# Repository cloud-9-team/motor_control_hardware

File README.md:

# Control de motores por comunicación Wi-Fi

Este proyecto forma parte de la cátedra de **Taller de Proyecto 1**, perteneciente al segundo semestre de la carrera de Ingeniería en Computación, en la Facultad de Ingeniería de la Universidad de La Plata. 

Nuestra motivación principal es lograr el **control de motores utilizando un tipo de comunicación inalámbrica**. La elección de dicha comunicación debe ser tal que se logre una abstracción del dispositivo desde el cual se envien los comandos de control. 
A partir de estas restricciones elegimos realizar el control de motores de corriente continua mediante el uso del protocolo de comunicación inalámbrica IEEE 802.11, comúnmente conocido cómo Wi-Fi. Al poder abstraernos del dispositivo que envía los comandos, se podrá hacer uso de **smartphones**, **servidores web**, o cualquier otro tipo de dispositivo que cuente con un protocolo de comunicación Wi-Fi integrado.

### Descripción 
En este proyecto se buscará desarrollar específicamente los siguientes puntos:
 - Control de dos motores de corriente continua a través de señales PWM utilizando un H-bridge IC L293D.
 - Comunicación mediante protocolo Wi-Fi con módulo independiente ESP8266.
 - Comunicación serie entre EDU-CIAA y módulo Wi-Fi.
 - Aplicación Android para comunicación con el módulo.

Estos dos últimos ítems se encuentran alojados en el siguiente repositorio https://github.com/cloud-9-team/motor_control_firmware_apps

### Esquema de funcionamiento
El funcionamiento del vehículo será controlado por **instrucciones AT** enviadas inalámbricamente por Wi-Fi desde un smartphone, corriendo un sistema operativo Android, al módulo ESP8266. El módulo ESP8266 enviará las instrucciones por **comunicación serie** a la EDU CIAA-NXP. La EDU CIAA procesará los comandos y, en base a eso, modificará los valores correspondientes de los cuatro outputs de SCT (módulo State Controlled Timer). Las señales serán enviadas a los inputs del H-bridge IC. El H-bridge, en base a la tensión media que reciba por sus entradas, permitirá a los dos motores girar en determinado sentido y con una cierta velocidad. Los sentidos y velocidades de los motores determinarán la dirección de movimiento del vehículo.

### Herramientas de desarrollo
Para el diseño del hardware se utiliza la herramienta de diseño asistido por computadora **Kicad**, y para el desarrollo del software el plugin de la CIAA para el entorno **Eclipse**.

### Integrantes del grupo

 - Julián Ailán
 - Federico Bouche
 - Lucas Hourquebie
 - Emiliano Liotta

### Descarga de los documentos
Debes tener **Git** instalado en tu máquina para poder gestionar las descargas. La instalación de Git depende del sistema operativo que uses
 - Distribuciones de Linux: 
    - En el caso de utilizar Fedora podes utilizar **yum**:
    ```sh
    $ sudo yum install git
    ```
    - En el caso de utilizar distribuciones basadas en Debian tenés que usar **apt-get**:
    ```sh
    $ sudo apt-get install git
    ```
 - Windows: accedé a http://git-scm.com/download/win y la instalación comenzará de forma automática.
 - MacOS: del mismo modo que en Windows, accedé a http://git-scm.com/download/mac y el instalador comenzará a descargarse.

Crear o posicionarse en la carpeta donde se desea descargar el contenido e inicializarla:
```sh
$ mkdir <nombre_de_la_carpeta>
$ cd <nombre_de_la_carpeta>
$ git init
```
Luego se debe relacionar el repositorio con la carpeta donde previamente te situaste:
```sh
$ git remote add origin https://github.com/cloud-9-team/motor_control_hardware.git
```
Por último, los contenidos se descargarán a la carpeta corriendo el siguiente comando:
```sh
$ git pull origin master
```
### Version
1.1

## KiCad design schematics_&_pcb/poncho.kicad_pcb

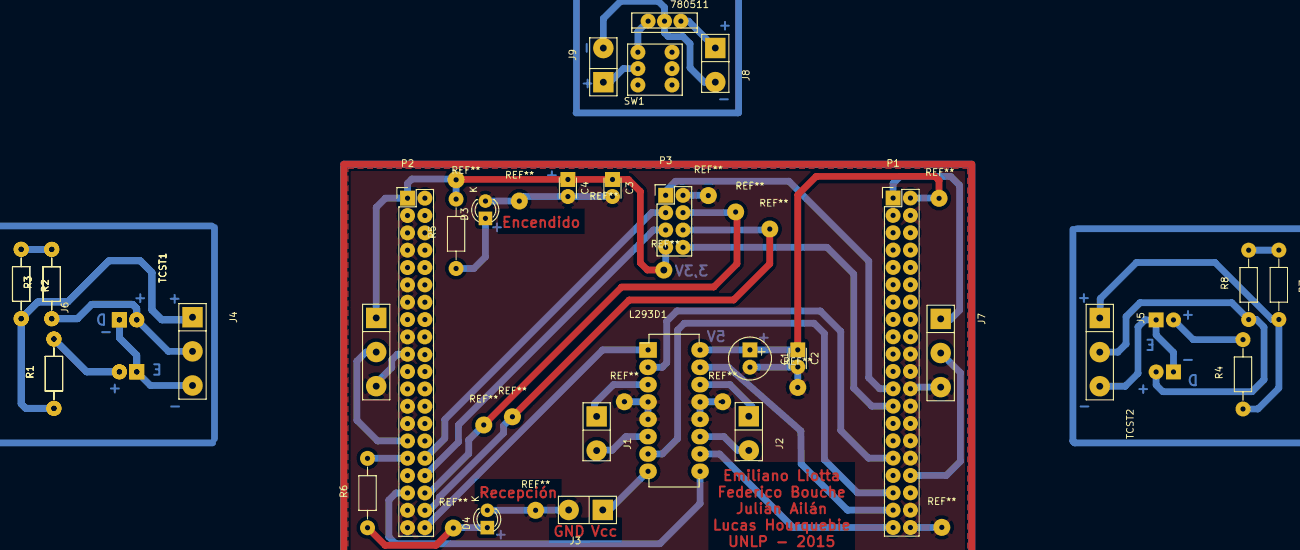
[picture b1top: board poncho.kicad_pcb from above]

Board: 2 copper layers, 35 parts (0 on the bottom side), 32 nets.

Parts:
780511: LM7805reg; LM7805
C1: CP; Elko_vert_11.2x6.3mm_RM2.5
C2, C3, C4: C; C_Disc_D3_P2.5
D3, D4: LED; LED-3MM
J1, J2, J3, J8, J9: TB_1X2; bornera1x2
J4, J5, J6, J7: TB_1X3; bornera1x3
L293D1: L293D; DIP-16_W7.62mm_LongPads
P1, P2: CONN_20X2; Pin_Header_Straight_2x20
P3: ESP8266; Pin_Header_Straight_2x04
R1, R1#2, R4: 180; Resistor_Horizontal_RM10mm
R2, R2#2, R7: 1k; Resistor_Horizontal_RM10mm
R3, R3#2, R8: 680; Resistor_Horizontal_RM10mm
R5, R6: R; Resistor_Horizontal_RM10mm
SW1: 6pin_switch
TCST1, TCST1#2, TCST2: TCST2103

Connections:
+3V3: C3.1, C4.1, J4.1, J5.1, J6.1, J7.1, P1.1, P2.1, P3.4, R1.1, R1#2.1, R2.2, R2#2.2, R4.1, R5.2, R7.2
+5V: C1.1, C2.1, L293D1.16, P1.2, P2.2
/ENG0_OUT0: J1.1, L293D1.3
/ENG0_OUT1: J1.2, L293D1.6
/ENG1_OUT0: J2.1, L293D1.14
/ENG1_OUT1: J2.2, L293D1.11
/GPIO0: J4.2, J6.2, P2.29, R3.1, R3#2.1, TCST1.3, TCST1#2.3
/GPIO1: P2.32, P3.2
/GPIO2: P2.31, R6.2
/GPIO3: P2.34, P3.3
/GPIO5: P2.36, P3.7
/GPIO6: L293D1.9, P2.35
/GPIO7: P2.38, P3.6
/GPIO8: L293D1.1, P2.40
/MOTOR_VCC: J3.1, L293D1.8
/RS232_RXD: P1.23, P3.1
/RS232_TXD: P1.25, P3.5
/TEC_COL0: L293D1.10, P1.39
/TEC_COL1: L293D1.2, P1.31
/TEC_COL2: J5.2, J7.2, P1.34, R8.1, TCST2.3
/TEC_F2: L293D1.15, P1.37
/TEC_F3: L293D1.7, P1.35
GND: C1.2, C2.2, C3.2, C4.2, D3.1, D4.1, J3.2, J4.3, J5.3, J6.3, J7.3, L293D1.4, L293D1.5, L293D1.12, L293D1.13, P1.4, P1.20, P1.22, P1.24, P1.26, P1.28, P1.30, P1.32, P1.38, P1.40, P2.3, P2.5, P2.7, P2.11, P2.13, P2.17, P2.19, P2.25, P2.27, P2.37, P2.39, P3.8, TCST1.2, TCST1.4, TCST1#2.2, TCST1#2.4, TCST2.2, TCST2.4
GNDA: P1.7, P1.8, P1.10, P1.12, P1.14, P1.16, P1.18
unnamed: J8.2, J9.2
unnamed: D3.2, R5.1
unnamed: D4.2, R6.1
unnamed: J9.1, SW1.2
unnamed: R1.2, R1#2.2, TCST1.1, TCST1#2.1
unnamed: R2.1, R2#2.1, R3.2, R3#2.2
unnamed: R4.2, TCST2.1
unnamed: R7.1, R8.2

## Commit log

2015-10-01 Documentos y codigo inicial agregados.
2015-10-01 Documentos de esquematicos del poncho sin terminar agregados.
2015-10-01 Cambios en el README.md
2015-10-03 Se agregaron modificaciones en los labels del .sch. [TODO] Averiguar como relacionar los resistores con su footprint correspontiente.
2015-10-05 Esquemático parcialmente terminado. [TODO] PCB.
2015-10-06 Esquemático terminado. Poncho agregado. [TODO] Corregir eventuales errores. Chequear que estén bien.
2015-10-07 Aplicación Android agregada
2015-10-09 Diagrama esquemático y PCB finalizados. [TODO] Verificar que sean correctos.
2015-10-09 Agregada aplicación Android para la comunicación TCP con módulo ESP8266
2015-10-22 Primer código integral para el control de motores.
2015-10-22 Pequeña modificación en archivos.
2015-10-22 Agregados pinouts de componentes utilizados
2015-10-22 Correciones en el PCB: tamaño de las coronas, pads para vias, ancho de los tracks.
2015-10-22 Agregado código fuente de aplicación Android para la comunicación TCP con el poncho
2015-10-22 Agregada comprimido de aplicación Android
2015-11-10 PCB modificado. [TODO] Verificar que esté correcto y proceder a armar la placa.
2015-11-12 .pcb y .sch modificados.
2015-11-21 Modificación del footprint del ESP8266, posición y conexión de los encoders.
2015-12-03 Poncho modificado a dos capas.
2015-12-03 Alimentación del módulo Wi-Fi corregida en PCB.
2015-12-29 Pines de la capa superior corregidos, cambio GPIO2 a GPIO6 para L293D, diodos agregados para alimentación y recepción, encoders con TCST2103 agregados, boton de encendido y regulador agregados.
2015-12-29 Borneras agregadas.
2015-12-30 Circuito de encendido modificado. Se invirtió el orden regulador/interruptor.
2016-02-09 Versión final del PCB.
2016-02-16 Corrección de warnings y rótulos. La aplicación Android se movió al repositorio de SW.
2016-02-16 README modificado.
2016-02-16 Datasheets faltantes agregados (lm7805, esp8266 y tcst2103).
